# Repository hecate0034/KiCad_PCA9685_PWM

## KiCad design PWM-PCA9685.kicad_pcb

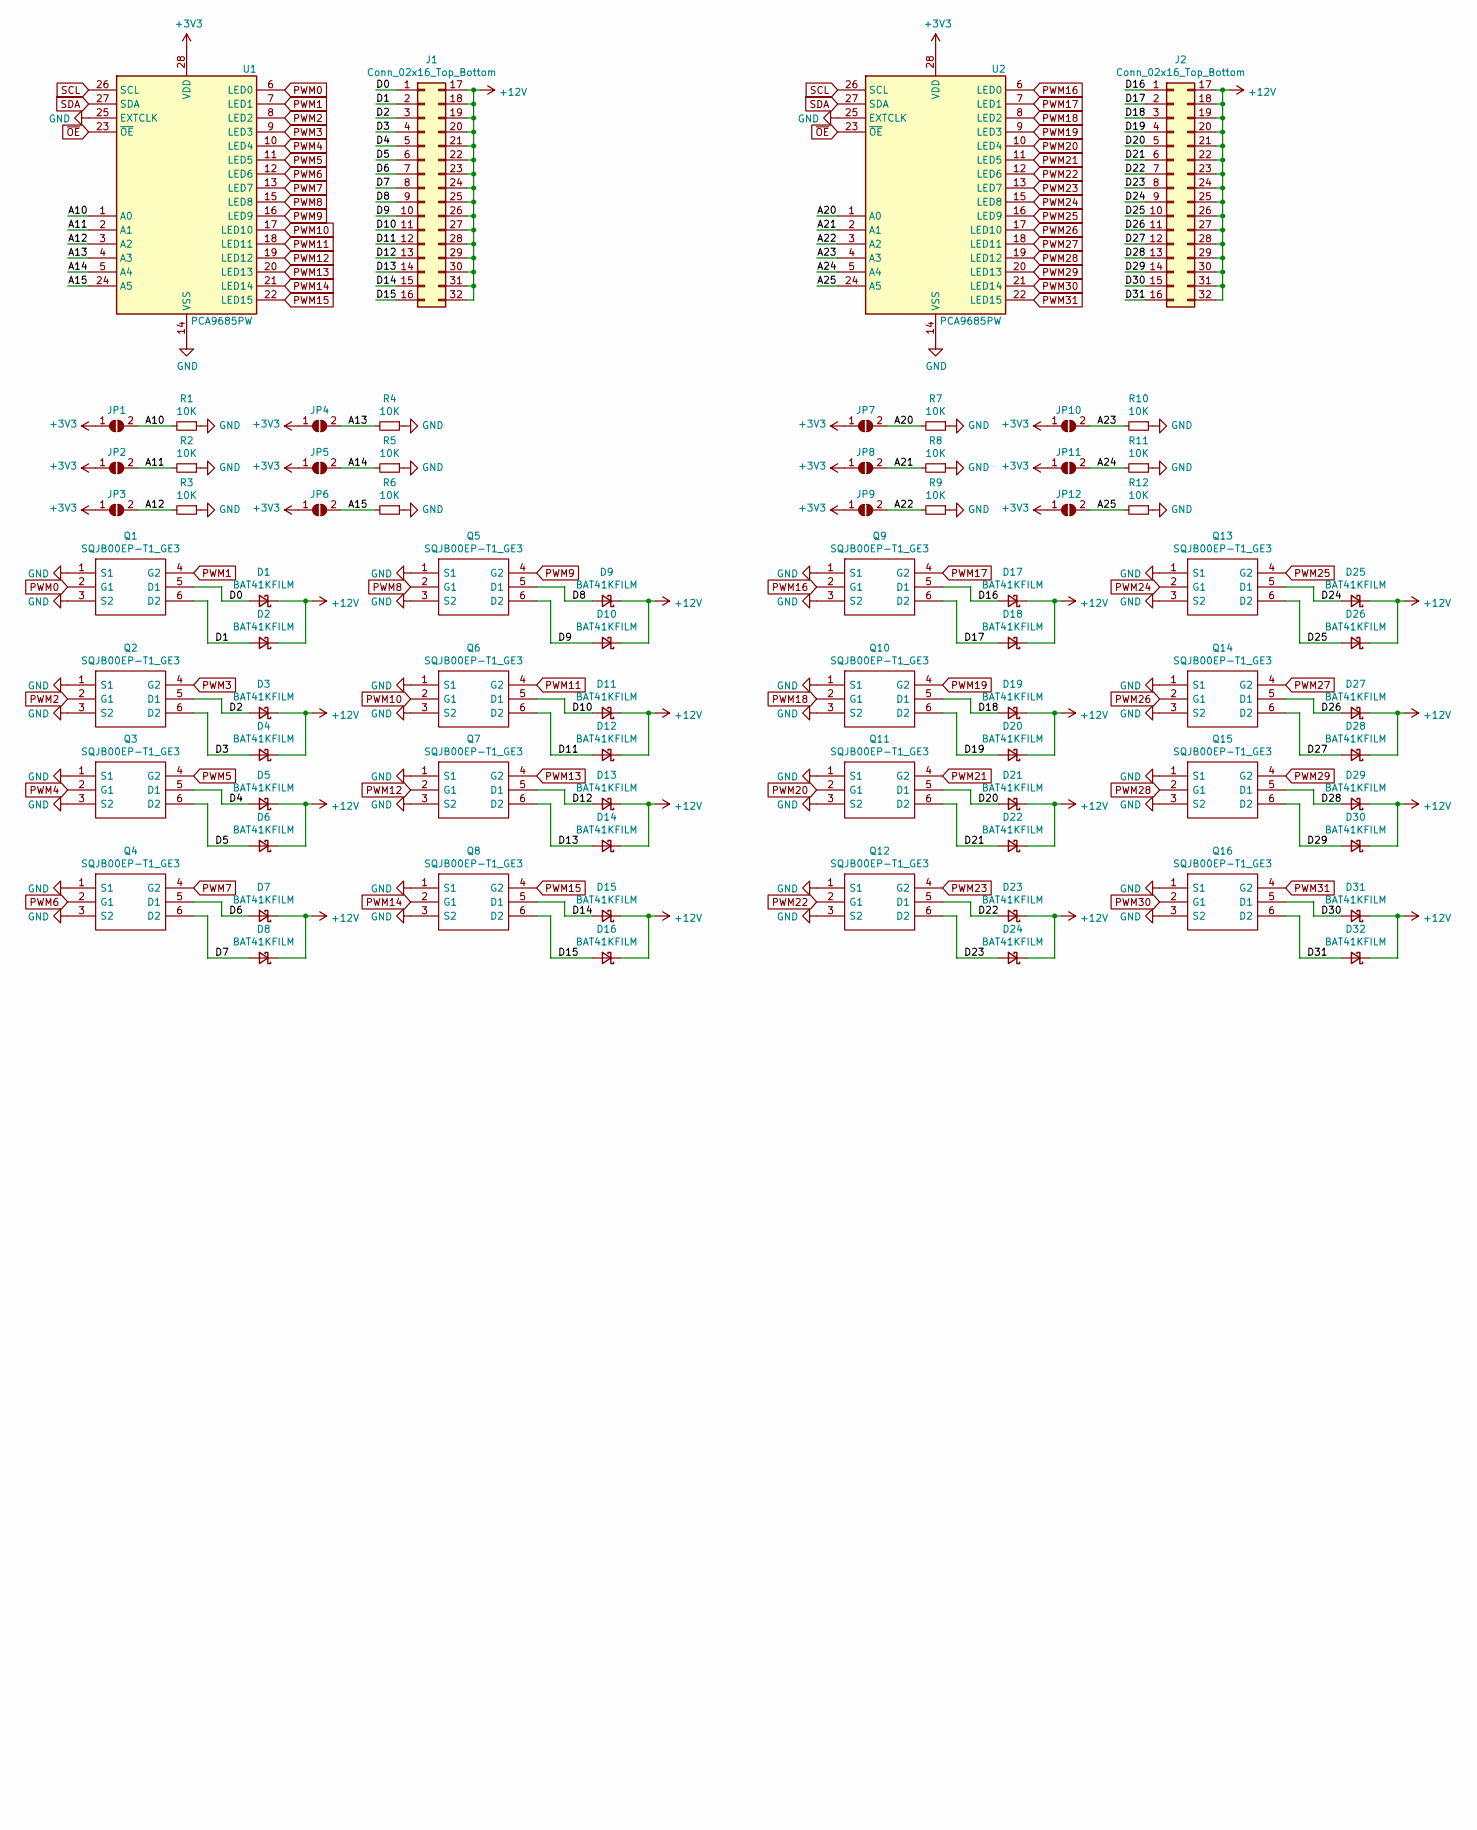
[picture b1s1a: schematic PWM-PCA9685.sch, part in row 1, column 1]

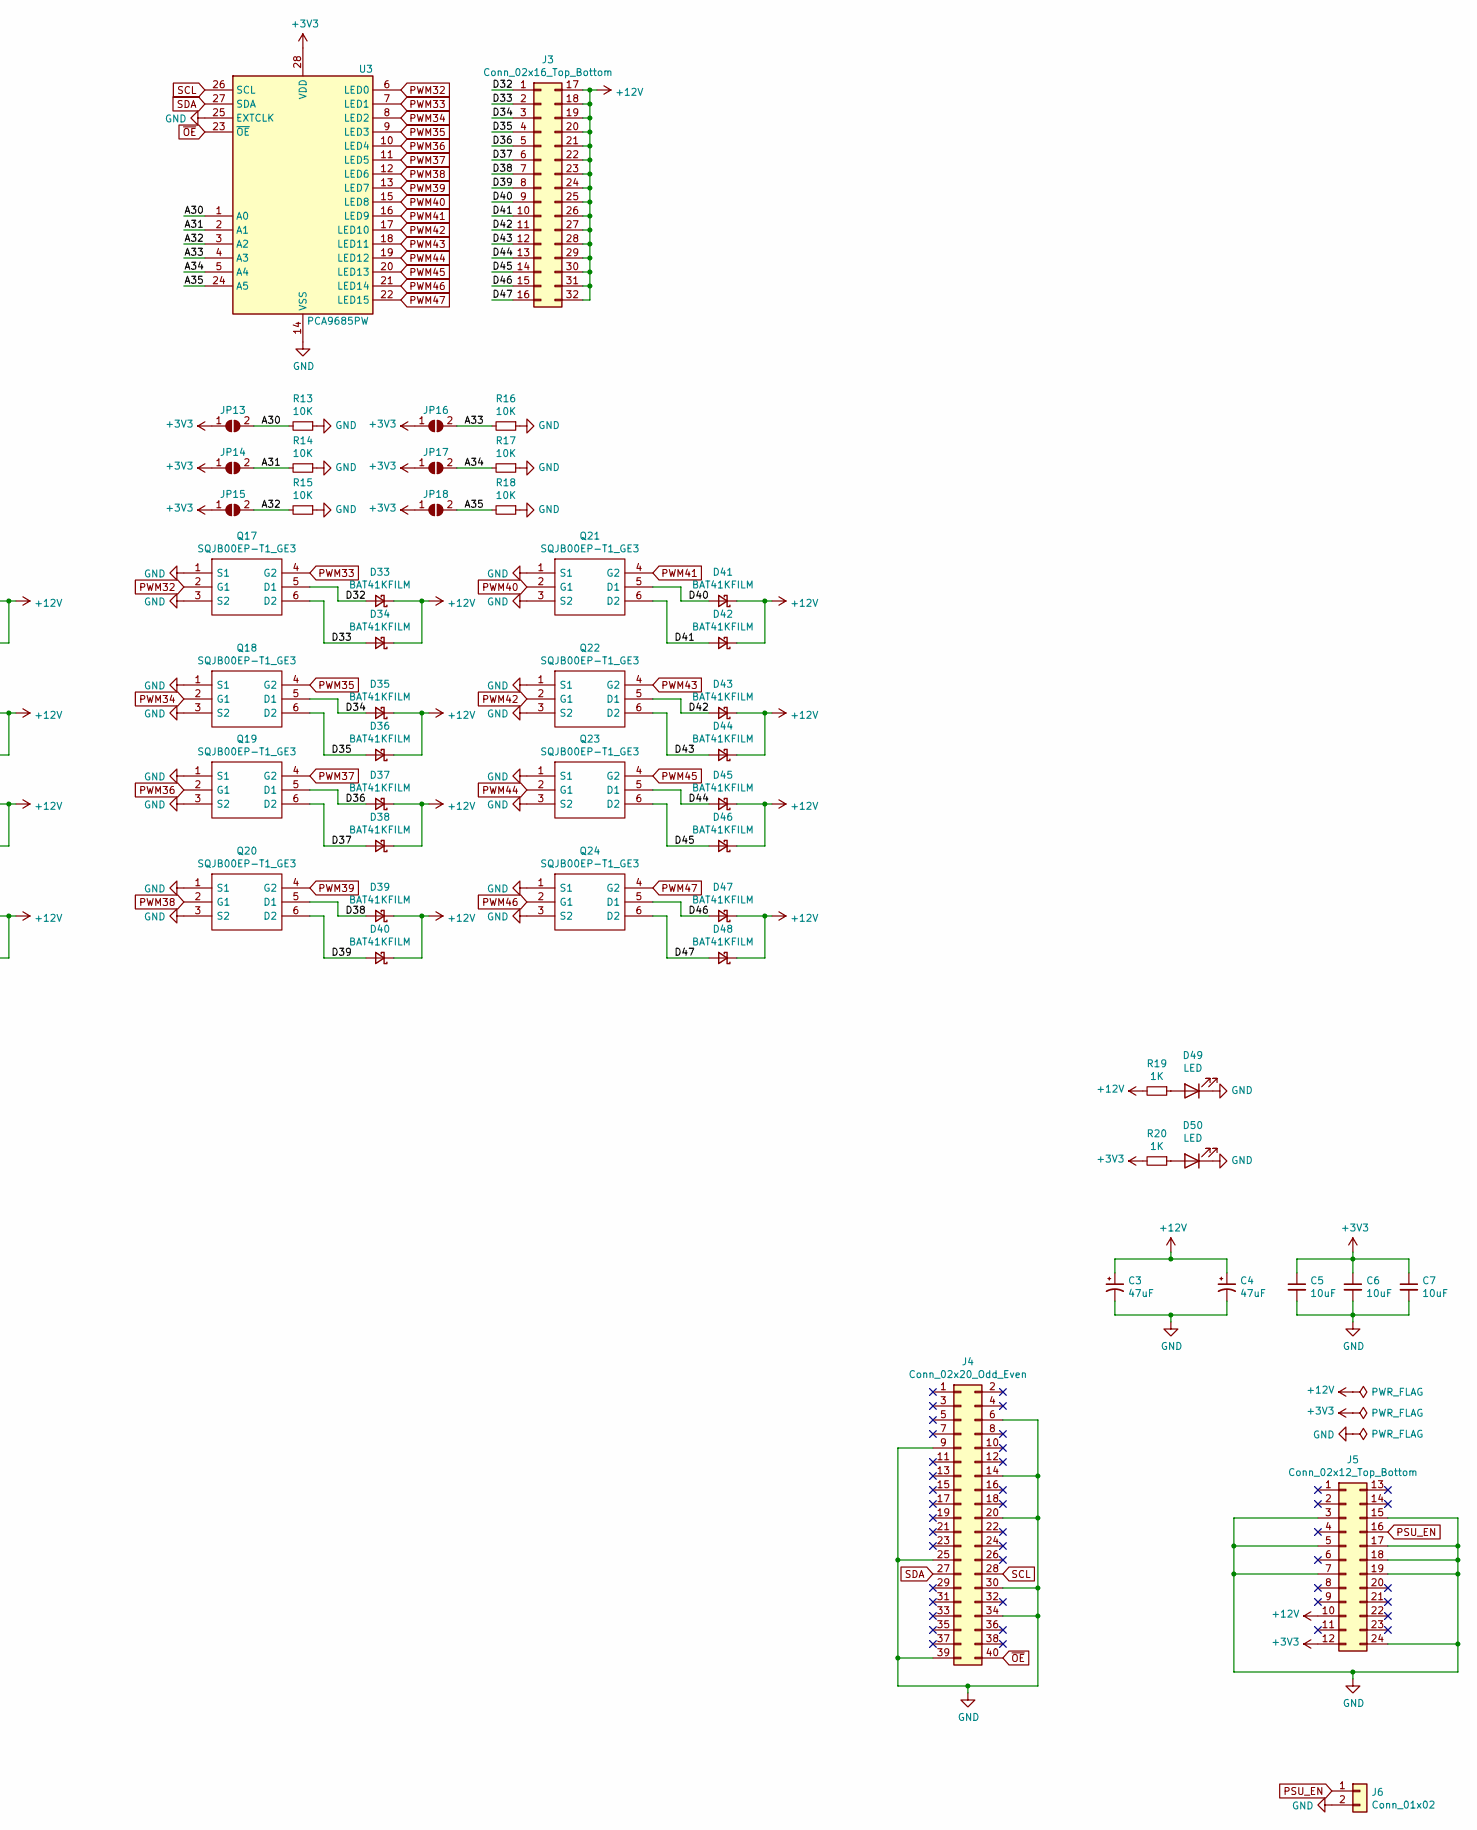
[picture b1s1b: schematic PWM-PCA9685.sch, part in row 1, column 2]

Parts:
C3, C4: 47uF; CP_Radial_D6.3mm_P2.50mm
C5, C6, C7: 10uF; C_1206_3216Metric
D1, D2, D3, D4, D5, D6, D7, D8, D9, D10, D11, D12, D13, D14, D15, D16, D17, D18, D19, D20, D21, D22, D23, D24, D25, D26, D27, D28, D29, D30, D31, D32, D33, D34, D35, D36, D37, D38, D39, D40, D41, D42, D43, D44, D45, D46, D47, D48: BAT41KFILM; D_SOD-523
D49, D50: LED; LED_0603_1608Metric
J1, J2, J3: Conn_02x16_Top_Bottom; PinSocket_2x16_P2.54mm_Vertical
J4: Conn_02x20_Odd_Even; PinSocket_2x20_P2.54mm_Vertical
J5: Conn_02x12_Top_Bottom; Molex_Mini-Fit_Jr_5566-24A2_2x12_P4.20mm_Vertical
J6: Conn_01x02; PinSocket_1x02_P2.54mm_Vertical
JP1, JP2, JP3, JP4, JP5, JP6, JP7, JP8, JP9, JP10, JP11, JP12, JP13, JP14, JP15, JP16, JP17, JP18: SolderJumper_2_Open; SolderJumper-2_P1.3mm_Open_Pad1.0x1.5mm
Q1, Q2, Q3, Q4, Q5, Q6, Q7, Q8, Q9, Q10, Q11, Q12, Q13, Q14, Q15, Q16, Q17, Q18, Q19, Q20, Q21, Q22, Q23, Q24: SQJB00EP-T1_GE3; SQJ968EPT1GE3; Manufacturer_Part_Number SQJB00EP-T1_GE3
R1, R2, R3, R4, R5, R6, R7, R8, R9, R10, R11, R12, R13, R14, R15, R16, R17, R18: 10K; R_0603_1608Metric
R19, R20: 1K; R_0603_1608Metric
U1, U2, U3: PCA9685PW; TSSOP-28_4.4x9.7mm_P0.65mm

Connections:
+3V3: C5.1, C6.1, C7.1, J5.12, JP1.1 (A), JP2.1 (A), JP3.1 (A), JP4.1 (A), JP5.1 (A), JP6.1 (A), JP7.1 (A), JP8.1 (A), JP9.1 (A), JP10.1 (A), JP11.1 (A), JP12.1 (A), JP13.1 (A), JP14.1 (A), JP15.1 (A), JP16.1 (A), JP17.1 (A), JP18.1 (A), R20.2, U1.28 (VDD), U2.28 (VDD), U3.28 (VDD)
+12V: C3.1, C4.1, D1.1 (K), D2.1 (K), D3.1 (K), D4.1 (K), D5.1 (K), D6.1 (K), D7.1 (K), D8.1 (K), D9.1 (K), D10.1 (K), D11.1 (K), D12.1 (K), D13.1 (K), D14.1 (K), D15.1 (K), D16.1 (K), D17.1 (K), D18.1 (K), D19.1 (K), D20.1 (K), D21.1 (K), D22.1 (K), D23.1 (K), D24.1 (K), D25.1 (K), D26.1 (K), D27.1 (K), D28.1 (K), D29.1 (K), D30.1 (K), D31.1 (K), D32.1 (K), D33.1 (K), D34.1 (K), D35.1 (K), D36.1 (K), D37.1 (K), D38.1 (K), D39.1 (K), D40.1 (K), D41.1 (K), D42.1 (K), D43.1 (K), D44.1 (K), D45.1 (K), D46.1 (K), D47.1 (K), D48.1 (K), J1.17, J1.18, J1.19, J1.20, J1.21, J1.22, J1.23, J1.24, J1.25, J1.26, J1.27, J1.28, J1.29, J1.30, J1.31, J1.32, J2.17, J2.18, J2.19, J2.20, J2.21, J2.22, J2.23, J2.24, J2.25, J2.26, J2.27, J2.28, J2.29, J2.30, J2.31, J2.32, J3.17, J3.18, J3.19, J3.20, J3.21, J3.22, J3.23, J3.24, J3.25, J3.26, J3.27, J3.28, J3.29, J3.30, J3.31, J3.32, J5.10, R19.2
/A10: JP1.2 (B), R1.2, U1.1 (A0)
/A11: JP2.2 (B), R2.2, U1.2 (A1)
/A12: JP3.2 (B), R3.2, U1.3 (A2)
/A13: JP4.2 (B), R4.2, U1.4 (A3)
/A14: JP5.2 (B), R5.2, U1.5 (A4)
/A15: JP6.2 (B), R6.2, U1.24 (A5)
/A20: JP7.2 (B), R7.2, U2.1 (A0)
/A21: JP8.2 (B), R8.2, U2.2 (A1)
/A22: JP9.2 (B), R9.2, U2.3 (A2)
/A23: JP10.2 (B), R10.2, U2.4 (A3)
/A24: JP11.2 (B), R11.2, U2.5 (A4)
/A25: JP12.2 (B), R12.2, U2.24 (A5)
/A30: JP13.2 (B), R13.2, U3.1 (A0)
/A31: JP14.2 (B), R14.2, U3.2 (A1)
/A32: JP15.2 (B), R15.2, U3.3 (A2)
/A33: JP16.2 (B), R16.2, U3.4 (A3)
/A34: JP17.2 (B), R17.2, U3.5 (A4)
/A35: JP18.2 (B), R18.2, U3.24 (A5)
/D0: D1.2 (A), J1.1, Q1.5 (D1)
/D1: D2.2 (A), J1.2, Q1.6 (D2)
/D2: D3.2 (A), J1.3, Q2.5 (D1)
/D3: D4.2 (A), J1.4, Q2.6 (D2)
/D4: D5.2 (A), J1.5, Q3.5 (D1)
/D5: D6.2 (A), J1.6, Q3.6 (D2)
/D6: D7.2 (A), J1.7, Q4.5 (D1)
/D7: D8.2 (A), J1.8, Q4.6 (D2)
/D8: D9.2 (A), J1.9, Q5.5 (D1)
/D9: D10.2 (A), J1.10, Q5.6 (D2)
/D10: D11.2 (A), J1.11, Q6.5 (D1)
/D11: D12.2 (A), J1.12, Q6.6 (D2)
/D12: D13.2 (A), J1.13, Q7.5 (D1)
/D13: D14.2 (A), J1.14, Q7.6 (D2)
/D14: D15.2 (A), J1.15, Q8.5 (D1)
/D15: D16.2 (A), J1.16, Q8.6 (D2)
/D16: D17.2 (A), J2.1, Q9.5 (D1)
/D17: D18.2 (A), J2.2, Q9.6 (D2)
/D18: D19.2 (A), J2.3, Q10.5 (D1)
/D19: D20.2 (A), J2.4, Q10.6 (D2)
/D20: D21.2 (A), J2.5, Q11.5 (D1)
/D21: D22.2 (A), J2.6, Q11.6 (D2)
/D22: D23.2 (A), J2.7, Q12.5 (D1)
/D23: D24.2 (A), J2.8, Q12.6 (D2)
/D24: D25.2 (A), J2.9, Q13.5 (D1)
/D25: D26.2 (A), J2.10, Q13.6 (D2)
/D26: D27.2 (A), J2.11, Q14.5 (D1)
/D27: D28.2 (A), J2.12, Q14.6 (D2)
/D28: D29.2 (A), J2.13, Q15.5 (D1)
/D29: D30.2 (A), J2.14, Q15.6 (D2)
/D30: D31.2 (A), J2.15, Q16.5 (D1)
/D31: D32.2 (A), J2.16, Q16.6 (D2)
/D32: D33.2 (A), J3.1, Q17.5 (D1)
/D33: D34.2 (A), J3.2, Q17.6 (D2)
/D34: D35.2 (A), J3.3, Q18.5 (D1)
/D35: D36.2 (A), J3.4, Q18.6 (D2)
/D36: D37.2 (A), J3.5, Q19.5 (D1)
/D37: D38.2 (A), J3.6, Q19.6 (D2)
/D38: D39.2 (A), J3.7, Q20.5 (D1)
/D39: D40.2 (A), J3.8, Q20.6 (D2)
/D40: D41.2 (A), J3.9, Q21.5 (D1)
/D41: D42.2 (A), J3.10, Q21.6 (D2)
/D42: D43.2 (A), J3.11, Q22.5 (D1)
/D43: D44.2 (A), J3.12, Q22.6 (D2)
/D44: D45.2 (A), J3.13, Q23.5 (D1)
/D45: D46.2 (A), J3.14, Q23.6 (D2)
/D46: D47.2 (A), J3.15, Q24.5 (D1)
/D47: D48.2 (A), J3.16, Q24.6 (D2)
GND: C3.2, C4.2, C5.2, C6.2, C7.2, D49.1 (K), D50.1 (K), J4.6, J4.9, J4.14, J4.20, J4.25, J4.30, J4.34, J4.39, J5.3, J5.5, J5.7, J5.15, J5.17, J5.18, J5.19, J5.24, J6.2, Q1.1 (S1), Q1.3 (S2), Q2.1 (S1), Q2.3 (S2), Q3.1 (S1), Q3.3 (S2), Q4.1 (S1), Q4.3 (S2), Q5.1 (S1), Q5.3 (S2), Q6.1 (S1), Q6.3 (S2), Q7.1 (S1), Q7.3 (S2), Q8.1 (S1), Q8.3 (S2), Q9.1 (S1), Q9.3 (S2), Q10.1 (S1), Q10.3 (S2), Q11.1 (S1), Q11.3 (S2), Q12.1 (S1), Q12.3 (S2), Q13.1 (S1), Q13.3 (S2), Q14.1 (S1), Q14.3 (S2), Q15.1 (S1), Q15.3 (S2), Q16.1 (S1), Q16.3 (S2), Q17.1 (S1), Q17.3 (S2), Q18.1 (S1), Q18.3 (S2), Q19.1 (S1), Q19.3 (S2), Q20.1 (S1), Q20.3 (S2), Q21.1 (S1), Q21.3 (S2), Q22.1 (S1), Q22.3 (S2), Q23.1 (S1), Q23.3 (S2), Q24.1 (S1), Q24.3 (S2), R1.1, R2.1, R3.1, R4.1, R5.1, R6.1, R7.1, R8.1, R9.1, R10.1, R11.1, R12.1, R13.1, R14.1, R15.1, R16.1, R17.1, R18.1, U1.14 (VSS), U1.25 (EXTCLK), U2.14 (VSS), U2.25 (EXTCLK), U3.14 (VSS), U3.25 (EXTCLK)
unnamed: D49.2 (A), R19.1
unnamed: D50.2 (A), R20.1
PSU_EN: J5.16, J6.1
PWM0: Q1.2 (G1), U1.6 (LED0)
PWM1: Q1.4 (G2), U1.7 (LED1)
PWM2: Q2.2 (G1), U1.8 (LED2)
PWM3: Q2.4 (G2), U1.9 (LED3)
PWM4: Q3.2 (G1), U1.10 (LED4)
PWM5: Q3.4 (G2), U1.11 (LED5)
PWM6: Q4.2 (G1), U1.12 (LED6)
PWM7: Q4.4 (G2), U1.13 (LED7)
PWM8: Q5.2 (G1), U1.15 (LED8)
PWM9: Q5.4 (G2), U1.16 (LED9)
PWM10: Q6.2 (G1), U1.17 (LED10)
PWM11: Q6.4 (G2), U1.18 (LED11)
PWM12: Q7.2 (G1), U1.19 (LED12)
PWM13: Q7.4 (G2), U1.20 (LED13)
PWM14: Q8.2 (G1), U1.21 (LED14)
PWM15: Q8.4 (G2), U1.22 (LED15)
PWM16: Q9.2 (G1), U2.6 (LED0)
PWM17: Q9.4 (G2), U2.7 (LED1)
PWM18: Q10.2 (G1), U2.8 (LED2)
PWM19: Q10.4 (G2), U2.9 (LED3)
PWM20: Q11.2 (G1), U2.10 (LED4)
PWM21: Q11.4 (G2), U2.11 (LED5)
PWM22: Q12.2 (G1), U2.12 (LED6)
PWM23: Q12.4 (G2), U2.13 (LED7)
PWM24: Q13.2 (G1), U2.15 (LED8)
PWM25: Q13.4 (G2), U2.16 (LED9)
PWM26: Q14.2 (G1), U2.17 (LED10)
PWM27: Q14.4 (G2), U2.18 (LED11)
PWM28: Q15.2 (G1), U2.19 (LED12)
PWM29: Q15.4 (G2), U2.20 (LED13)
PWM30: Q16.2 (G1), U2.21 (LED14)
PWM31: Q16.4 (G2), U2.22 (LED15)
PWM32: Q17.2 (G1), U3.6 (LED0)
PWM33: Q17.4 (G2), U3.7 (LED1)
PWM34: Q18.2 (G1), U3.8 (LED2)
PWM35: Q18.4 (G2), U3.9 (LED3)
PWM36: Q19.2 (G1), U3.10 (LED4)
PWM37: Q19.4 (G2), U3.11 (LED5)
PWM38: Q20.2 (G1), U3.12 (LED6)
PWM39: Q20.4 (G2), U3.13 (LED7)
PWM40: Q21.2 (G1), U3.15 (LED8)
PWM41: Q21.4 (G2), U3.16 (LED9)
PWM42: Q22.2 (G1), U3.17 (LED10)
PWM43: Q22.4 (G2), U3.18 (LED11)
PWM44: Q23.2 (G1), U3.19 (LED12)
PWM45: Q23.4 (G2), U3.20 (LED13)
PWM46: Q24.2 (G1), U3.21 (LED14)
PWM47: Q24.4 (G2), U3.22 (LED15)
SCL: J4.28, U1.26 (SCL), U2.26 (SCL), U3.26 (SCL)
SDA: J4.27, U1.27 (SDA), U2.27 (SDA), U3.27 (SDA)
~OE: J4.40, U1.23 (~OE), U2.23 (~OE), U3.23 (~OE)

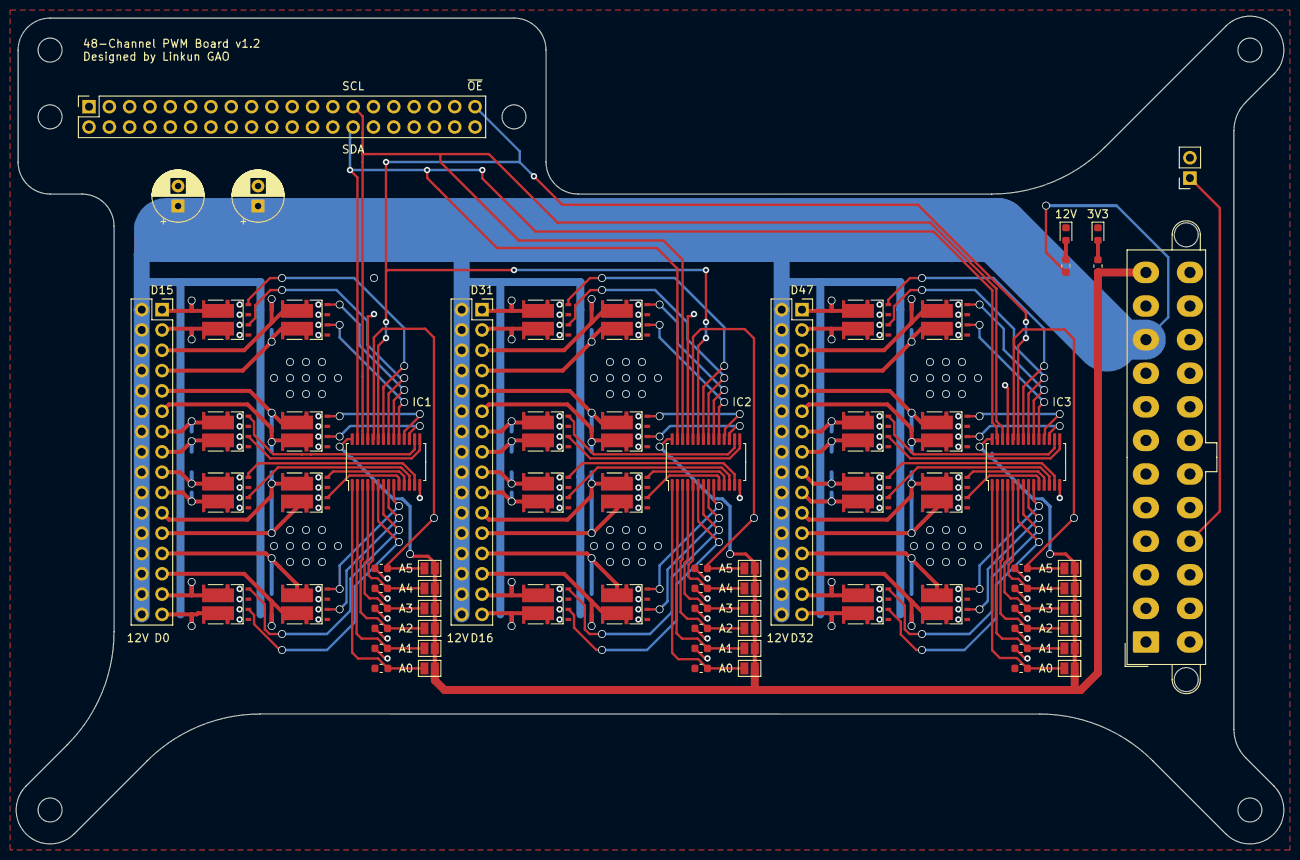
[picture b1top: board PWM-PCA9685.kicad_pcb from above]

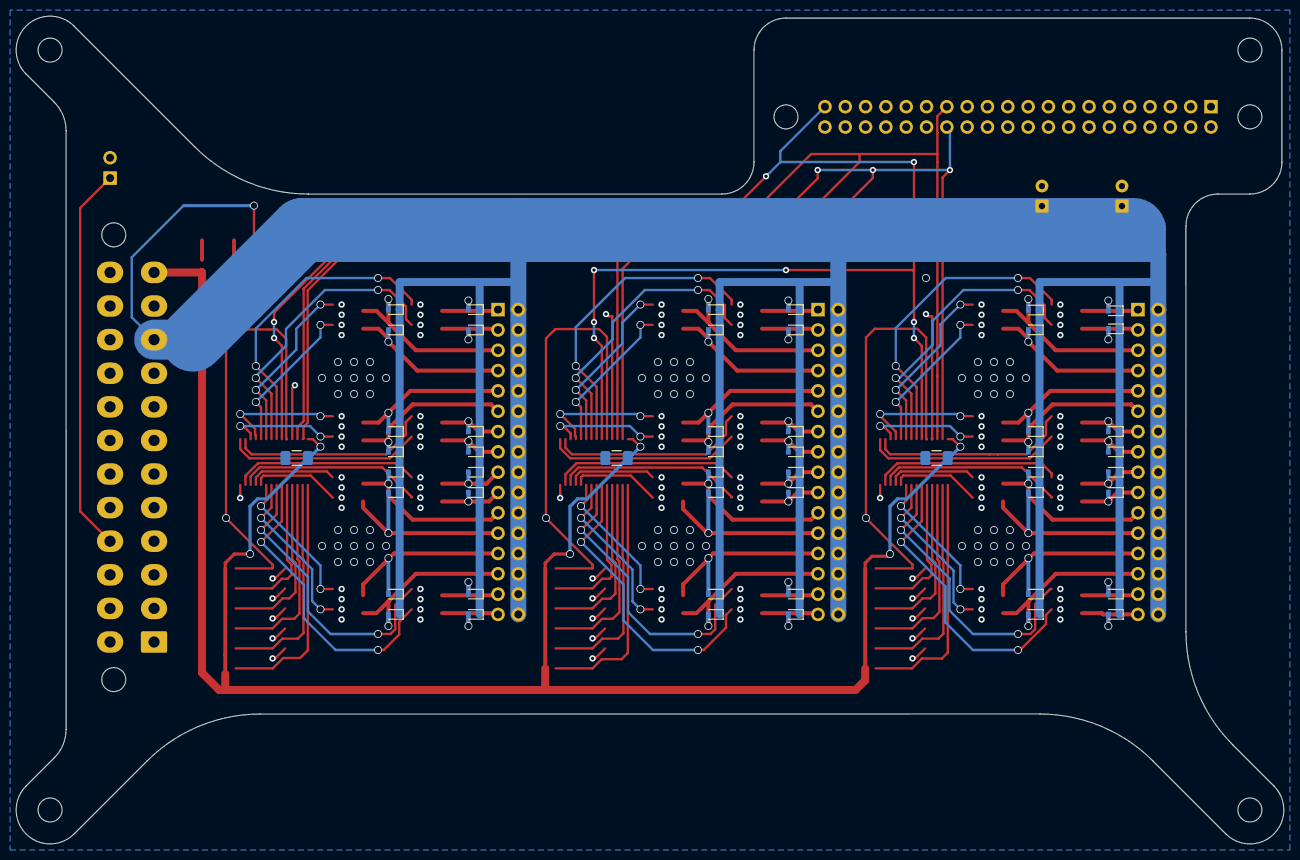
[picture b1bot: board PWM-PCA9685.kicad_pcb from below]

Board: 2 copper layers, 158.5 x 103.5 mm, 126 parts (51 on the bottom side), 123 nets.

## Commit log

2020-07-21 v1.2 3v3 compatible
